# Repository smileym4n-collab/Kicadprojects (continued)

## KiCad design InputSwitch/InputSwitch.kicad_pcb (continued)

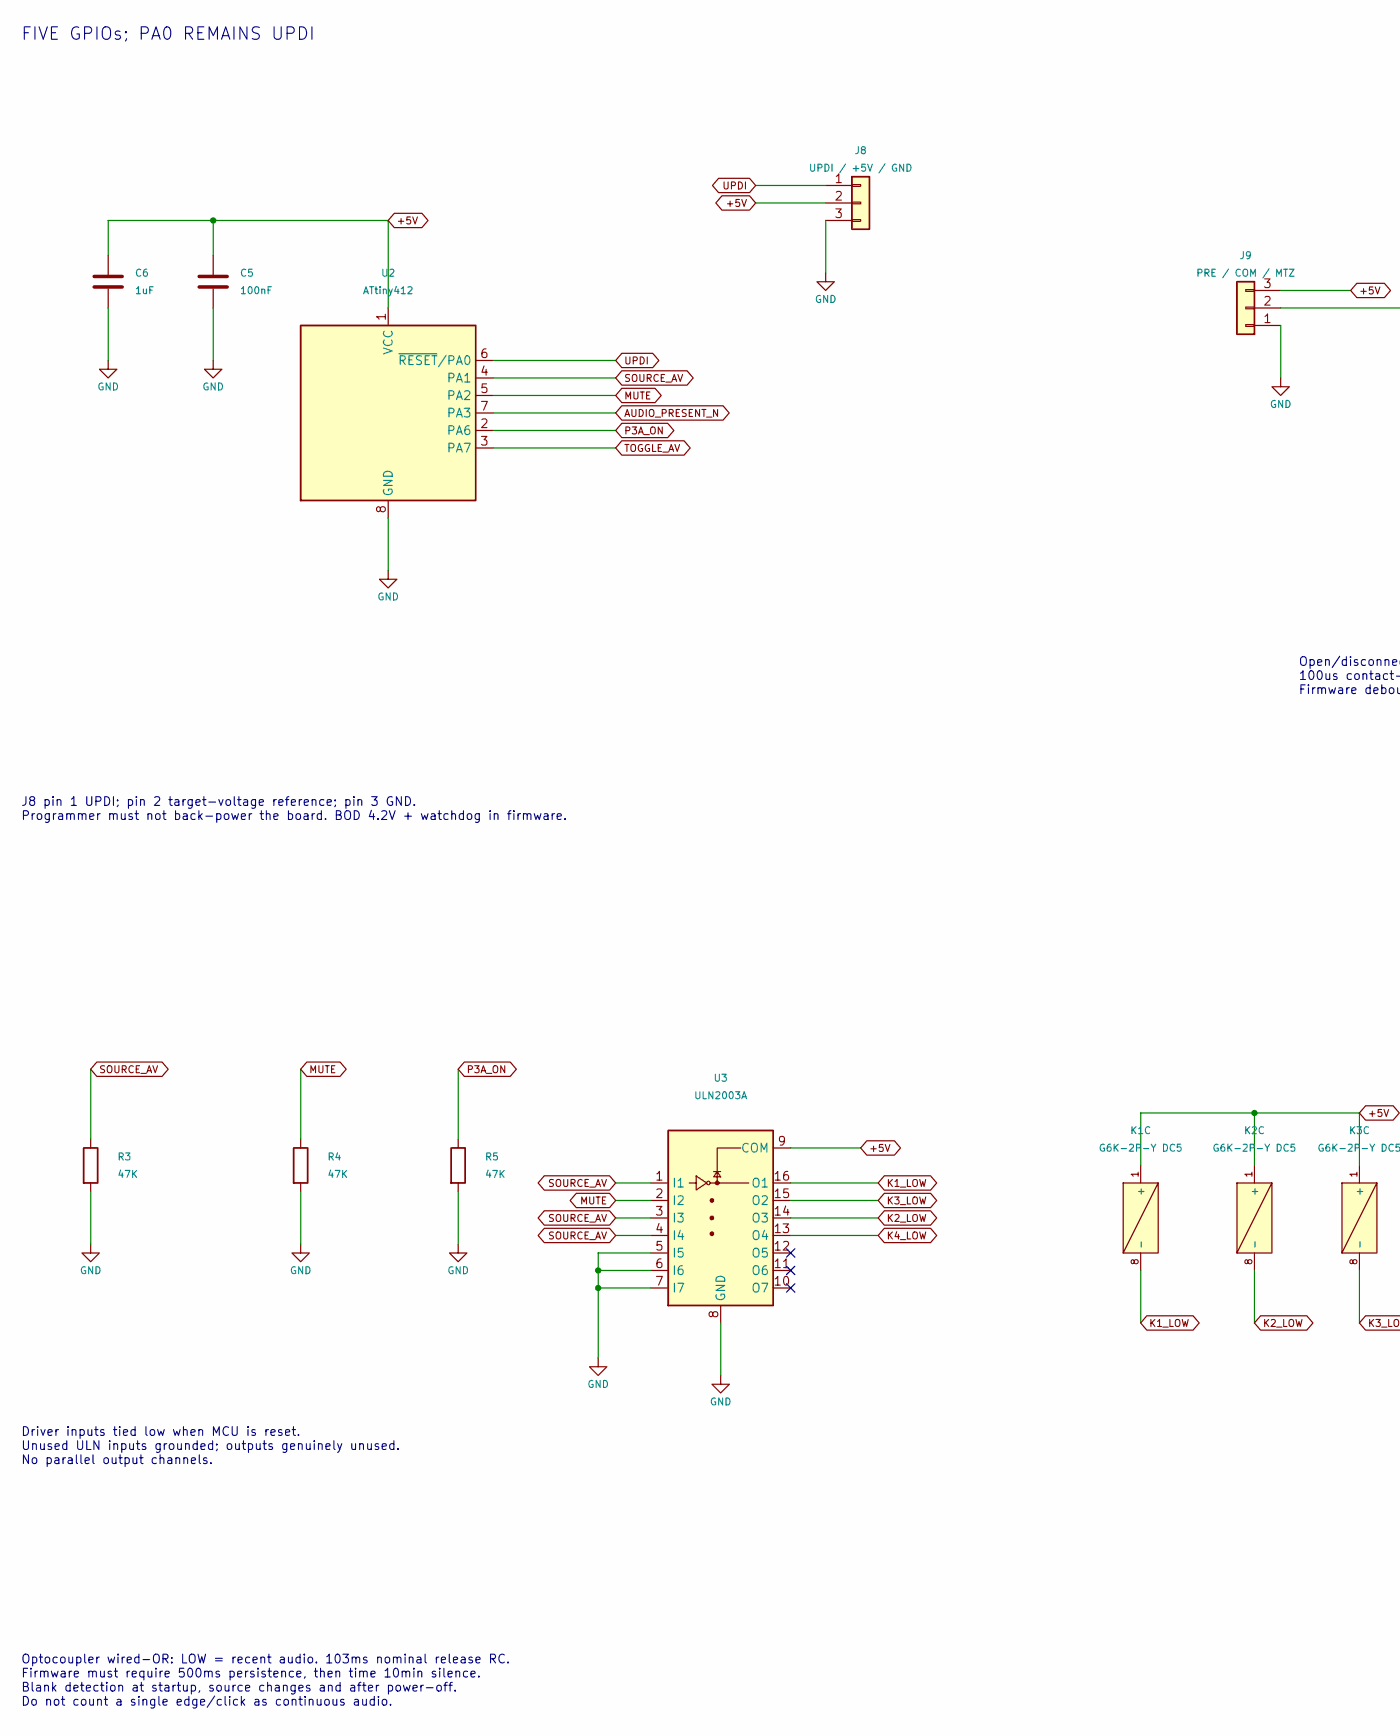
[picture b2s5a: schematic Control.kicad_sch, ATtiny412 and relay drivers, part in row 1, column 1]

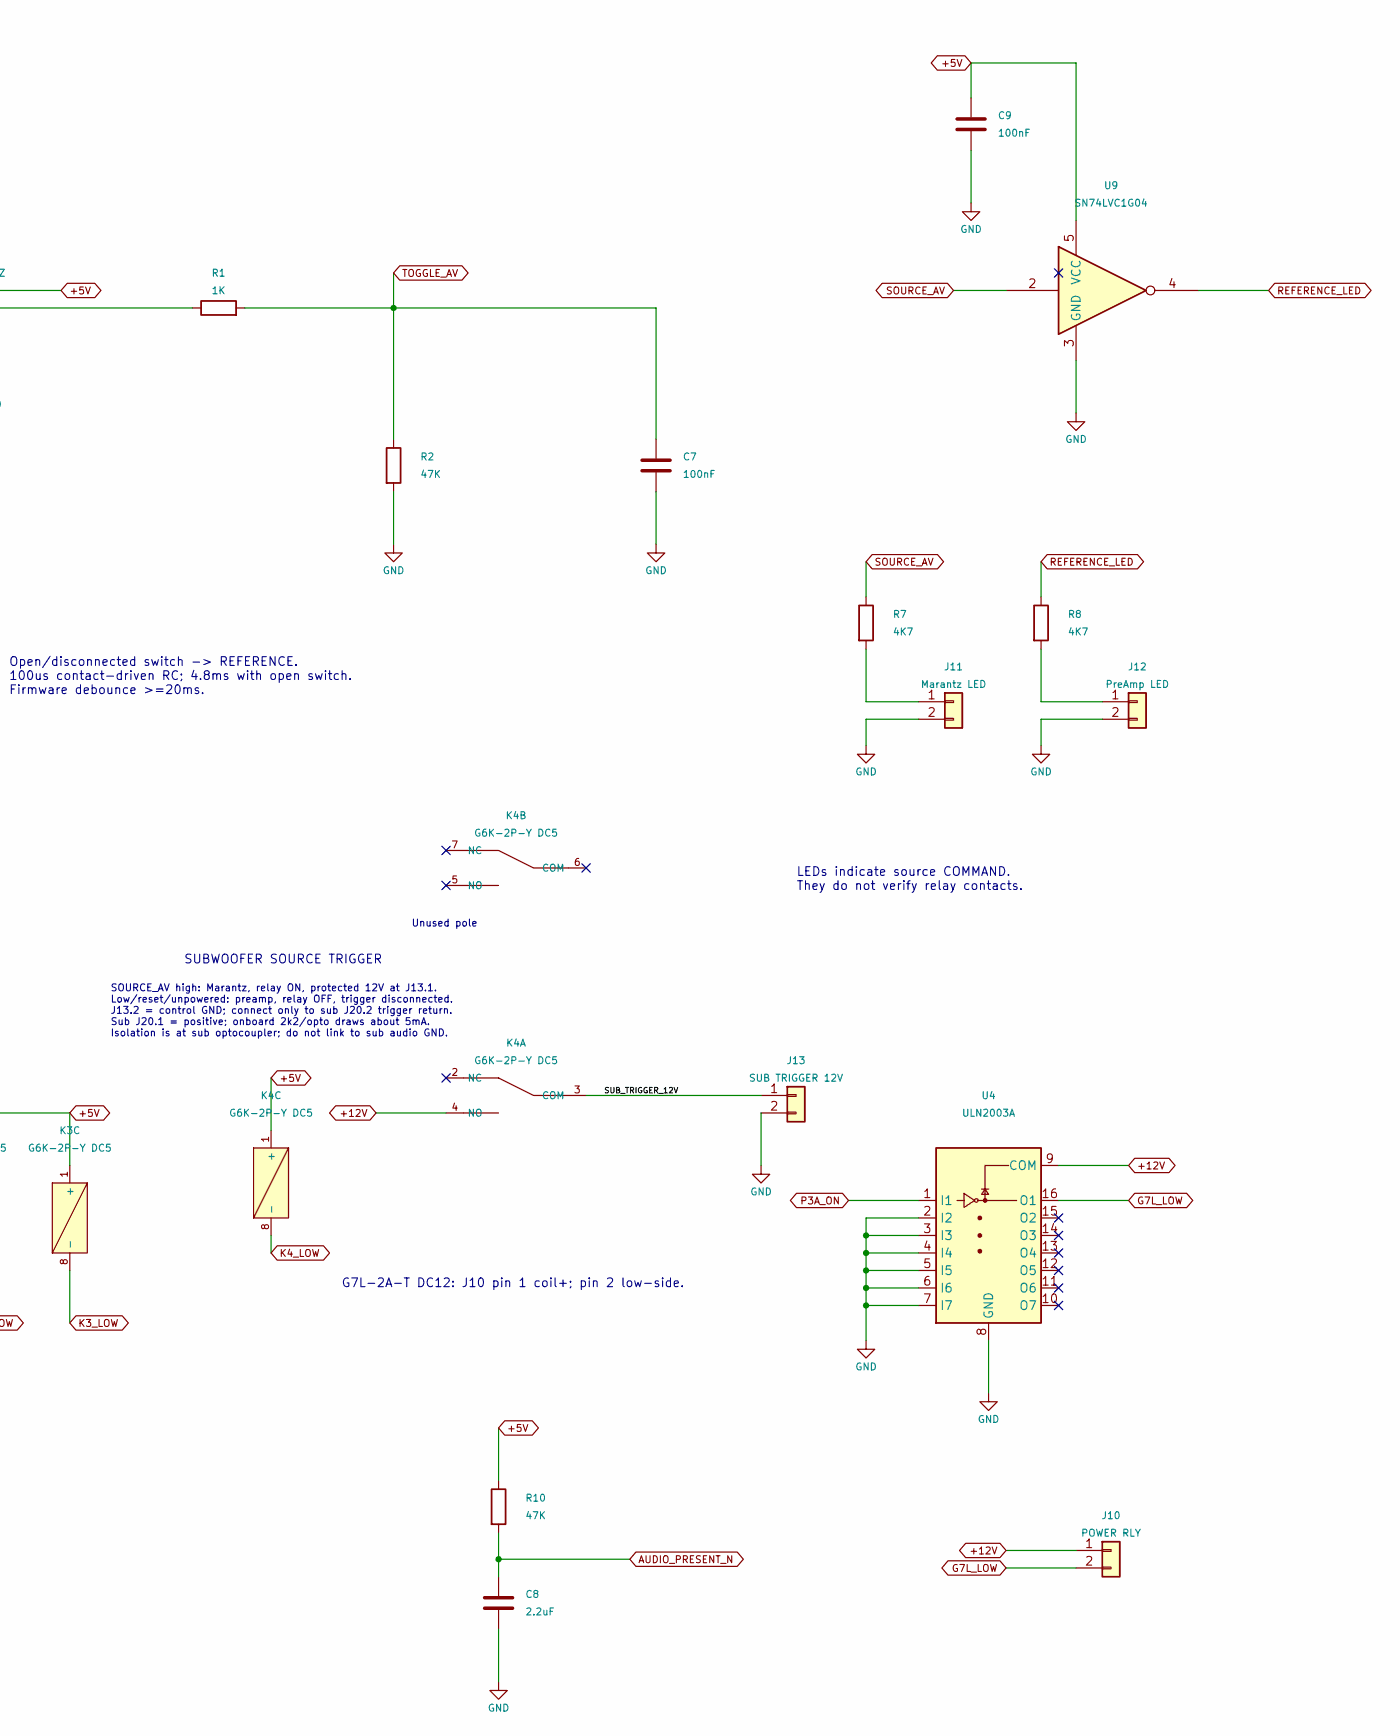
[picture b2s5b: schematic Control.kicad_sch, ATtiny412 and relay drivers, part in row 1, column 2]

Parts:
C5, C7, C9: 100nF; C_1206_3216Metric_Pad1.33x1.80mm_HandSolder
C6: 1uF; C_1206_3216Metric_Pad1.33x1.80mm_HandSolder
C8: 2.2uF; C_0805_2012Metric_Pad1.18x1.45mm_HandSolder
J8: UPDI / +5V / GND; JST_XH_B3B-XH-A_1x03_P2.50mm_Vertical
J9: PRE / COM / MTZ; JST_XH_B3B-XH-A_1x03_P2.50mm_Vertical
J10: POWER RLY; JST_XH_B2B-XH-A_1x02_P2.50mm_Vertical
J11: Marantz LED; JST_XH_B2B-XH-A_1x02_P2.50mm_Vertical
J12: PreAmp LED; JST_XH_B2B-XH-A_1x02_P2.50mm_Vertical
J13: SUB TRIGGER 12V; JST_XH_B2B-XH-A_1x02_P2.50mm_Vertical
K1, K2, K3, K4: G6K-2P-Y DC5; Relay_DPDT_Omron_G6K-2P-Y_Datasheet
R1: 1K; R_0805_2012Metric_Pad1.20x1.40mm_HandSolder
R2, R3, R4, R5, R10: 47K; R_0805_2012Metric_Pad1.20x1.40mm_HandSolder
R7, R8: 4K7; R_0805_2012Metric_Pad1.20x1.40mm_HandSolder
U2: ATtiny412; SOIC-8_3.9x4.9mm_P1.27mm
U3, U4: ULN2003A; SOIC-16_3.9x9.9mm_P1.27mm
U9: SN74LVC1G04; SOT-23-5

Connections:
+5V: C5.1, C6.1, C9.1, J8.2, J9.3, K1.1 (+), K2.1 (+), K3.1 (+), K4.1 (+), R10.1, U2.1 (VCC), U3.9 (COM), U9.5 (VCC); also elsewhere on the board
+12V: J10.1, K4.4 (NO), U4.9 (COM); also elsewhere on the board
/ATtiny412 and relay drivers/SUB_TRIGGER_12V: J13.1, K4.3 (COM)
AUDIO_PRESENT_N: C8.1, R10.2, U2.7 (PA3); also elsewhere on the board
G7L_LOW: J10.2, U4.16 (O1)
GND: C5.2, C6.2, C7.2, C8.2, C9.2, J8.3, J9.1, J11.2, J12.2, J13.2, R2.2, R3.2, R4.2, R5.2, U2.8 (GND), U3.5 (I5), U3.6 (I6), U3.7 (I7), U3.8 (GND), U4.2 (I2), U4.3 (I3), U4.4 (I4), U4.5 (I5), U4.6 (I6), U4.7 (I7), U4.8 (GND), U9.3 (GND); also elsewhere on the board
K1_LOW: K1.8 (-), U3.16 (O1)
K2_LOW: K2.8 (-), U3.14 (O3)
K3_LOW: K3.8 (-), U3.15 (O2)
K4_LOW: K4.8 (-), U3.13 (O4)
MUTE: R4.1, U2.5 (PA2), U3.2 (I2)
unnamed: J9.2, R1.1
unnamed: J11.1, R7.2
unnamed: J12.1, R8.2
P3A_ON: R5.1, U2.2 (PA6), U4.1 (I1)
REFERENCE_LED: R8.1, U9.4
SOURCE_AV: R3.1, R7.1, U2.4 (PA1), U3.1 (I1), U3.3 (I3), U3.4 (I4), U9.2
TOGGLE_AV: C7.1, R1.2, R2.1, U2.3 (PA7)
UPDI: J8.1, U2.6 (~RESET/PA0)

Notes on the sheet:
SUBWOOFER SOURCE TRIGGER
J8 pin 1 UPDI; pin 2 target-voltage reference; pin 3 GND. Programmer must not back-power the board. BOD 4.2V + watchdog in firmware.
FIVE GPIOs; PA0 REMAINS UPDI
LEDs indicate source COMMAND. They do not verify relay contacts.
G7L-2A-T DC12: J10 pin 1 coil+; pin 2 low-side.
Unused pole
Driver inputs tied low when MCU is reset. Unused ULN inputs grounded; outputs genuinely unused. No parallel output channels.
Open/disconnected switch -> REFERENCE. 100us contact-driven RC; 4.8ms with open switch. Firmware debounce >=20ms.
SOURCE_AV high: Marantz, relay ON, protected 12V at J13.1. Low/reset/unpowered: preamp, relay OFF, trigger disconnected. J13.2 = control GND; connect only to sub J20.2 trigger return. Sub J20.1 = positive; onboard 2k2/opto draws about 5mA. Isolation is at sub optocoupler; do not link to sub audio G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
Optocoupler wired-OR: LOW = recent audio. 103ms nominal release RC. Firmware must require 500ms persistence, then time 10min silence. Blank detection at startup, source changes and after power-off. Do not count a single edge/click as continuous audio.

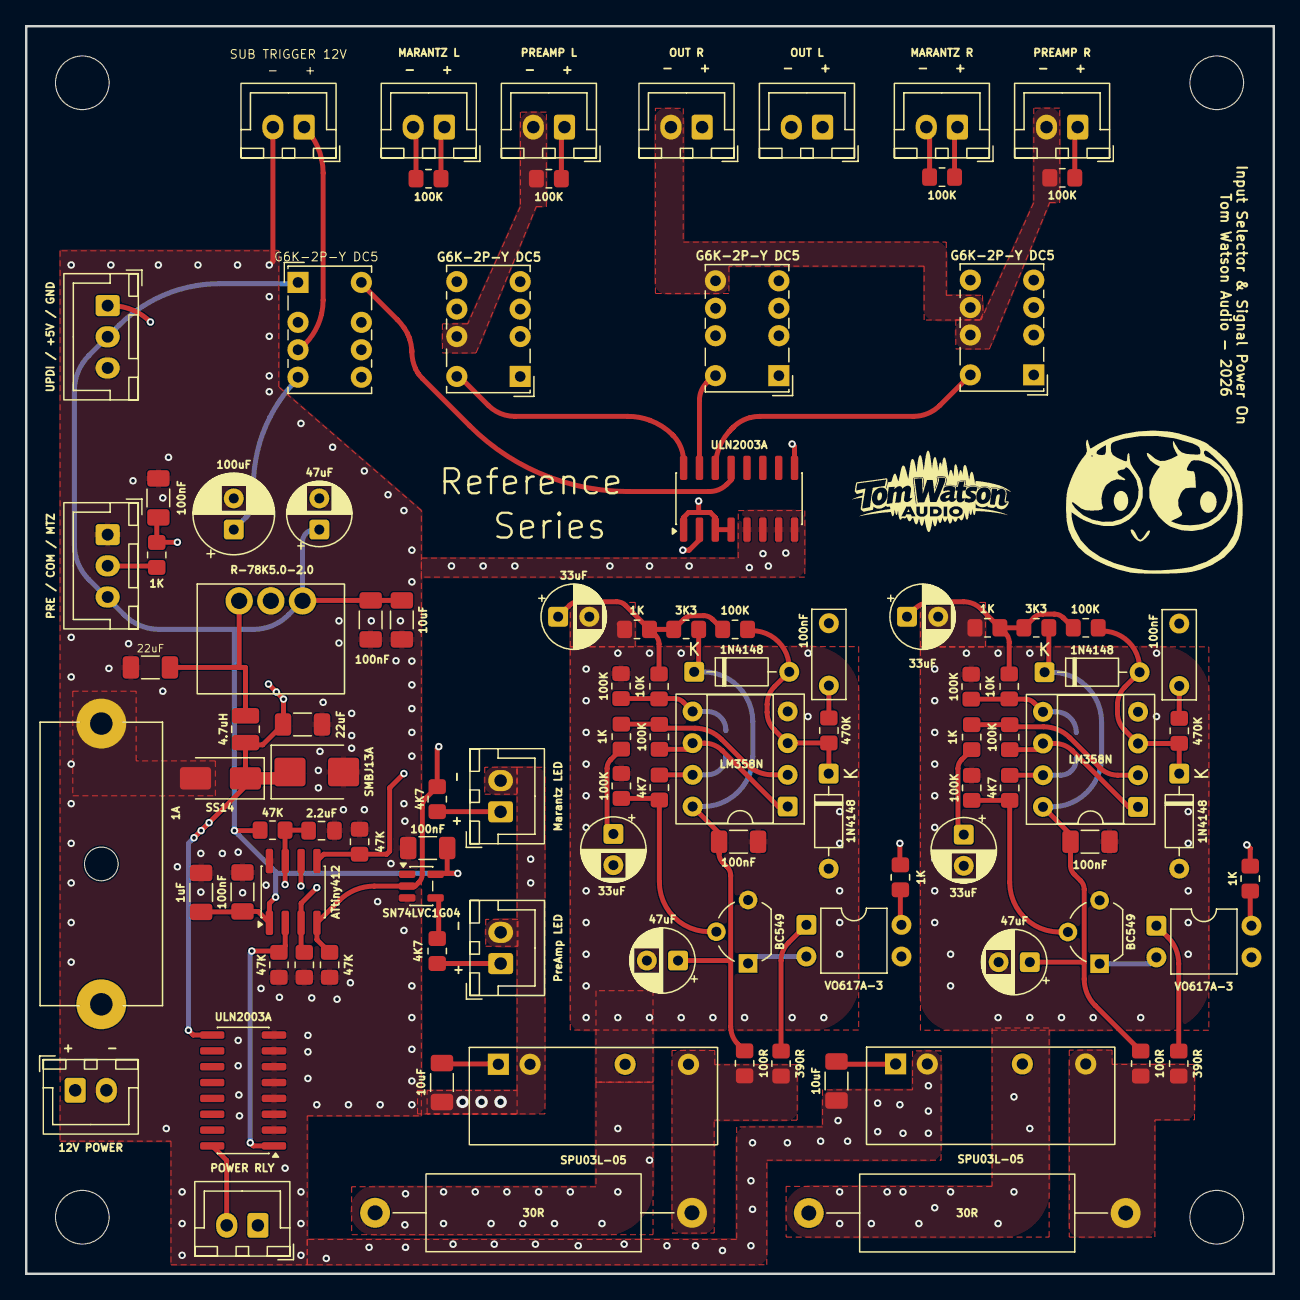
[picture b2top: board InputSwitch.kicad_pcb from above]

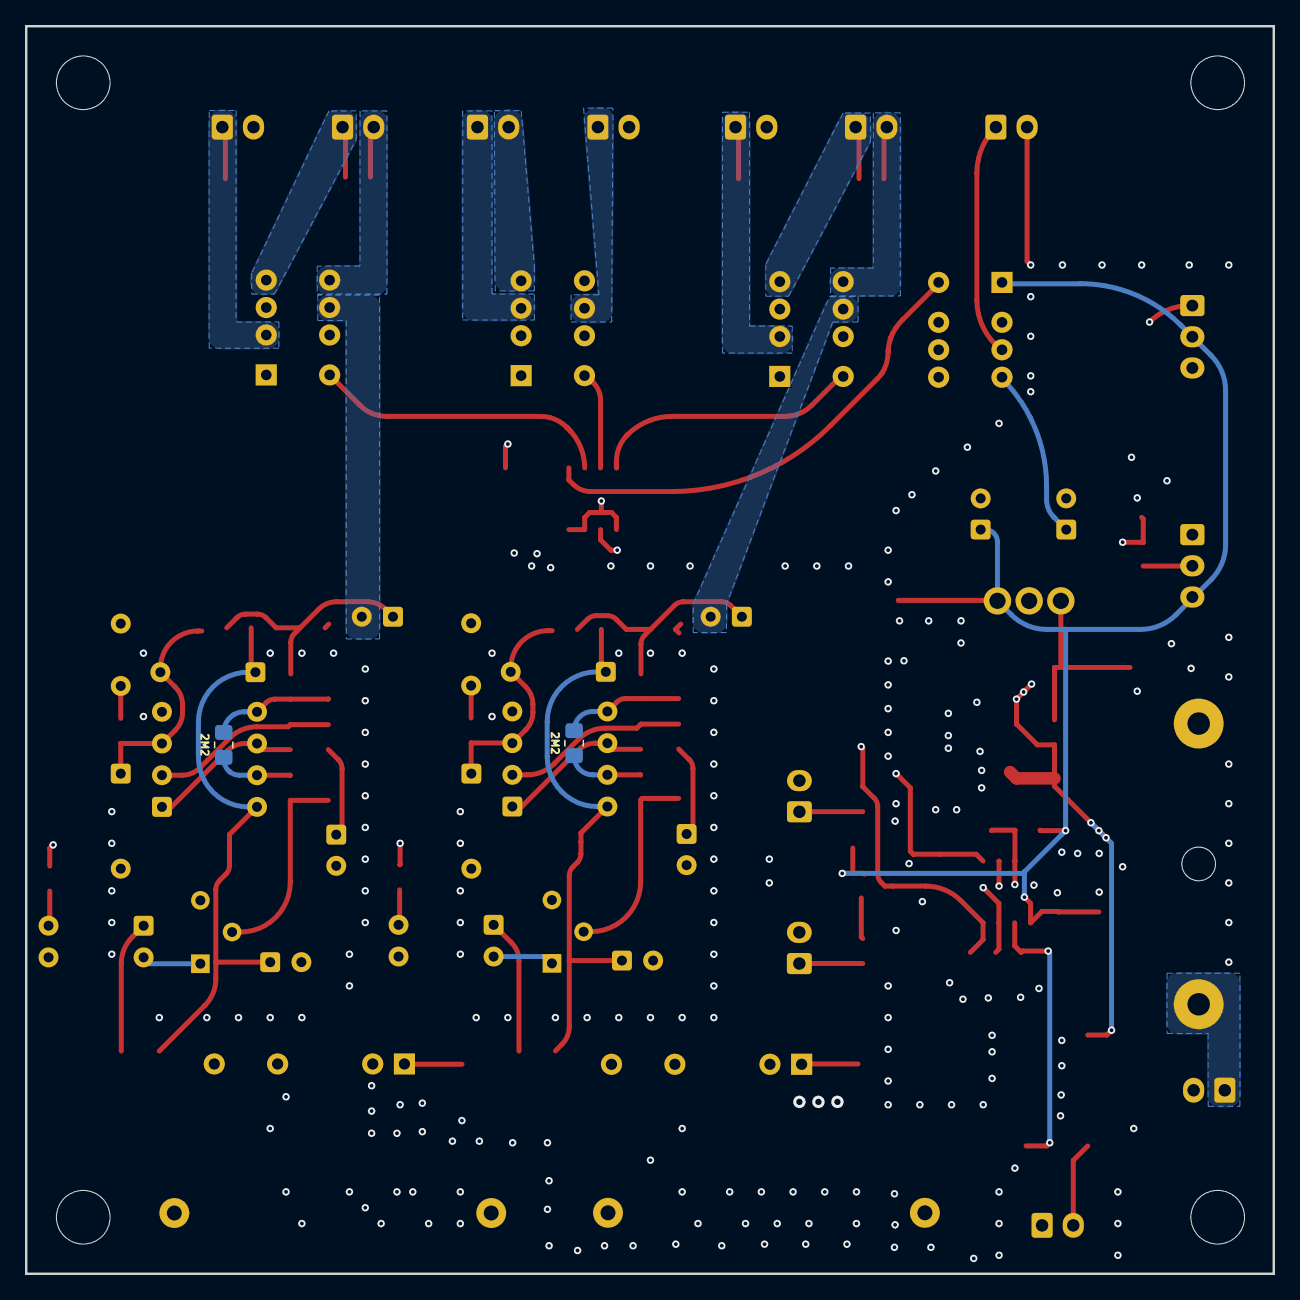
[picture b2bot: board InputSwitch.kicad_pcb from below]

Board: 4 copper layers, 100.0 x 100.0 mm, 107 parts (2 on the bottom side), 64 nets.

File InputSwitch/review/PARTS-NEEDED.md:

# InputSwitch parts needed

Inventory was checked live during this review. No stock was reserved or consumed and no orders were placed. Quantities listed as available are inventory records, not physical inspection. Match package and suffix exactly before assembly.

## Main purchases not found in inventory

| Qty | Part | Purpose / package |
|---:|---|---|
| 2 | Vishay **VO617A-3** | Detector optocouplers; standard DIP-4, 7.62 mm row spacing. |
| 1 | RECOM **R-78B5.0-2.0** | 12 V to 5 V buck module, SIP3, 2 A. Larger body than original 500 mA module; correct footprint assigned. |
| 1 | TI **SN74LVC1G04DBVR** | Source-LED inverter, DBV / SOT-23-5. |
| 2 | Vishay **PR03, 30R, 3W, 1%, copper leads** | Flameproof preload resistors; DIN0617, 25.4 mm formed pitch. Confirm exact suffix; 3 W rating requires copper-lead version. |
| 1 | Vishay **SS14** | Reverse-polarity blocking diode, SMA. No inventory hit in the initial search. |
| 1 | Littelfuse **SMBJ13A** | Unidirectional input TVS, SMB. |
| 1 | Omron **G7L-2A-T DC12** | External mains relay; no inventory record found. Omit purchase if already physically owned. |

**No isolated converters or 5.1 V reference zeners need to be bought.** Use two owned SPU03L-05 modules; one remains spare. Inventory ID416 is labelled “SPI03L-05”; the user identified the physical units as SPU03L-05. The inventory record was not edited.

Supplier references: [VO617A-3 at DigiKey UK](https://www.digikey.co.uk/en/products/detail/vishay-semicond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, [R-78B5.0-2.0 at DigiKey](https://www.digikey.com/en/products/detail/recom-power/R-78B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, [R-78B manufacturer](https://recom-power.com/en/rec-p-R-78B5.0-2.0.html), [PR03 manufacturer specification](https://www.vishay.com/docs/28729/pr010203.pdf). Confirm current UK stock, exact suffix and price before ordering. No suitable 30R power resistor was found in the inventory search; 330R and 0R33 records are not substitutes.

## Reuse from recorded stock

| Need | Inventory record | Recorded stock | Package / location |
|---:|---|---:|---|
| 3 | G6K-2P-Y, 5 V, ID 420 | 4, none reserved | Through-hole; location not recorded |
| 1 | ATtiny412, ID 80 | 6, none reserved | SOIC-8; SMD Parts |
| 2 | ULN2003A, ID 121 | 7, none reserved | ST SOIC-16; SMD Parts |
| 2 | SPU03L-05 (recorded SPI03L-05), ID 416 | 3, none reserved | SIP7; Voltage regulator drawer |
| 2 | LM358, ID 389 | 2, none reserved | TI DIP-8; Opamp drawer |
| 2 | BC549, ID 452 | 117, none reserved | TO-92; manufacturer/location not recorded |
| 4 | 1N4148, ID 138 | 63, none reserved | Through-hole; Parts drawer 2 |

The five DIP-16 ULN2003As (ID 120, Mixed ICs drawer) are not the package assigned in this schematic. Use the SOIC-16 stock above unless a package change is approved. Check the physical G6K markings really say DC5 and the BC549 lead order is C-B-E before assembly. The two LM358s use the entire recorded unreserved quantity. Five unreserved MCP6002 DIP-8 devices were also found (ID13, Opamps drawer); no op-amp substitution is necessary. See [suitability review](SPU03-LM358-REVIEW.md).

## Other build items

- Six two-pin JST XH headers for audio and two more for DC input/G7L coil; two three-pin JST XH headers for UPDI and toggle, with matching housings/crimps.
- SPDT ON-ON front toggle, two suitable indicator LEDs, six isolated RCA sockets or existing system harnesses, shielded audio wiring.
- Regulated isolated 12 V wall adapter, preferably ±2%, at least 1 A; suitable DC inlet/cable.
- T1A 5 x 20 mm fuse and holder. **Holder provision needs mechanical confirmation:** the assigned FX0457 library footprint and Bulgin's conflicting online orientation descriptions need comparison with the actual part/drawing before purchase/layout.
- Three test-point pins/pads and existing mounting hardware.
- Passives listed below; check drawer stock by exact value/rating before buying. SMD resistors and ceramics are **2012 metric**. The two 30R preload resistors are through-hole, 3 W, 1%; mount with ventilation and clearance from capacitors. They dissipate approximately 0.83 W each at nominal voltage. Use 1% resistors; thin-film in detector gain/threshold networks is sensible. No precision parts are needed in utility pull-downs or LED feeds.
- Main input capacitor C1: 100 µF / 35 V, 6.3 mm body, 2.5 mm lead spacing provision. Other radial electrolytics currently use 5 mm body / 2.5 mm pitch provisions. Confirm exact bought capacitor dimensions. C24/C44 are detector-branch film capacitors; their 5 mm pitch / body provision also needs an exact-part fit check.

The following grouped BOM is generated from the final exported netlist, so quantities and references correspond to the schematic. It is an assembly planning BOM, not an order-ready manufacturer-part-number BOM.

| Qty | Value / part | References | Package / provision |
|---:|---|---|---|
| 1 | +12V | TP1 | TestPoint_THTPad_D2.0mm_Drill1.0mm |
| 1 | +5V | TP2 | TestPoint_THTPad_D2.0mm_Drill1.0mm |
| 2 | 100R | R21, R41 | 2012 metric |
| 8 | 100k | R24, R25, R28, R31, R44, R45, R48, R51 | 2012 metric |
| 6 | 100n / 50V | C22, C4, C42, C5, C7, C9 | 2012 metric |
| 2 | 100n FILM / 50V | C24, C44 | C_Rect_L7.0mm_W2.0mm_P5.00mm |
| 1 | 100u / 35V | C1 | CP_Radial_D6.3mm_P2.50mm |
| 2 | 10k | R27, R47 | 2012 metric |
| 3 | 10u / 50V X7R | C2, C20, C40 | 2012 metric |
| 1 | 12V DC INPUT | J7 | JST_XH_B2B-XH-A_1x02_P2.50mm_Vertical |
| 4 | 1N4148 | D21, D22, D41, D42 | D_DO-35_SOD27_P7.62mm_Horizontal |
| 7 | 1k | R1, R26, R33, R34, R46, R53, R54 | 2012 metric |
| 1 | 1u / 25V | C6 | 2012 metric |
| 2 | 2M2 | R29, R49 | 2012 metric |
| 1 | 2u2 / 25V | C8 | 2012 metric |
| 2 | 30R / 3W / 1% | R20, R40 | R_Axial_DIN0617_L17.0mm_D6.0mm_P25.40mm_Horizontal |
| 4 | 33u / 16V | C23, C25, C43, C45 | CP_Radial_D5.0mm_P2.50mm |
| 2 | 390R | R32, R52 | 2012 metric |
| 2 | 3k3 | R22, R42 | 2012 metric |
| 2 | 470k | R23, R43 | 2012 metric |
| 5 | 47k | R10, R2, R3, R4, R5 | 2012 metric |
| 1 | 47u / 16V | C3 | CP_Radial_D5.0mm_P2.50mm |
| 2 | 47u / 25V | C21, C41 | CP_Radial_D5.0mm_P2.50mm |
| 4 | 4k7 | R30, R50, R7, R8 | 2012 metric |
| 1 | ATtiny412-SS | U2 | SOIC-8_3.9x4.9mm_P1.27mm |
| 1 | AV | D3 | LED_D3.0mm |
| 1 | AV L | J2 | JST_XH_B2B-XH-A_1x02_P2.50mm_Vertical |
| 1 | AV R | J4 | JST_XH_B2B-XH-A_1x02_P2.50mm_Vertical |
| 2 | BC549 | Q2, Q3 | TO-92_Inline |
| 3 | G6K-2P-Y DC5 | K1, K2, K3 | Relay_DPDT_Omron_G6K-2P-Y |
| 1 | G7L COIL ONLY | J10 | JST_XH_B2B-XH-A_1x02_P2.50mm_Vertical |
| 1 | GND | TP3 | TestPoint_THTPad_D2.0mm_Drill1.0mm |
| 2 | LM358N | U5, U7 | DIP-8_W7.62mm |
| 4 | M4 | H1, H2, H3, H4 | MountingHole_4.3mm_M4 |
| 1 | P3A L | J5 | JST_XH_B2B-XH-A_1x02_P2.50mm_Vertical |
| 1 | P3A R | J6 | JST_XH_B2B-XH-A_1x02_P2.50mm_Vertical |
| 1 | R-78B5.0-2.0 | U1 | R78B_2A_SIP3 |
| 1 | REFERENCE | D4 | LED_D3.0mm |
| 1 | REFERENCE L | J1 | JST_XH_B2B-XH-A_1x02_P2.50mm_Vertical |
| 1 | REFERENCE R | J3 | JST_XH_B2B-XH-A_1x02_P2.50mm_Vertical |
| 1 | SMBJ13A | D2 | D_SMB |
| 1 | SN74LVC1G04DBV | U9 | SOT-23-5 |
| 1 | SPDT: REF / COM / AV | J9 | JST_XH_B3B-XH-A_1x03_P2.50mm_Vertical |
| 2 | SPU03L-05 | U10, U11 | SPU03L_05_SIP7 |
| 1 | SS14 | D1 | D_SMA |
| 1 | T1A | F1 | Fuseholder_Cylinder-5x20mm_Bulgin_FX0457_Horizontal_Closed |
| 1 | ULN2003A (12V COIL) | U4 | SOIC-16_3.9x9.9mm_P1.27mm |
| 1 | ULN2003A (5V COILS) | U3 | SOIC-16_3.9x9.9mm_P1.27mm |
| 1 | UPDI / +5V / GND | J8 | JST_XH_B3B-XH-A_1x03_P2.50mm_Vertical |
| 2 | VO617A-3 | U6, U8 | DIP-4_W7.62mm |

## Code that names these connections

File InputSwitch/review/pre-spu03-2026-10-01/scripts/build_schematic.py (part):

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 nc,co,no=(2,3,4) if ch=='L' else (7,6,5)
 a.net(mute,nc,'SEL_'+ch+'_SIGNAL',-8,0)
 jrout=conn(a,'J5' if ch=='L' else 'J6','P3A '+ch,143,y,rot=0)
 a.w(a.p(mute,co),a.p(jrout,1));a.label('P3A_'+ch+'_SIGNAL',a.at(125,y))
 p=a.p(mute,no);b=a.at(102,y+6);d=a.at(137,y+6)
 a.w(p,a.at(102,y+1),b,d,a.at(137,y+1),a.p(jrout,2));a.w(b,(b[0],b[1]+2*U));a.label('SEL_'+ch+'_RETURN',(b[0],b[1]+2*U),True)
 a.text(ch+' channel: no common GND',8,y+22)
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 else:s.net(tp,1,net,0,3)
s.text('NO PCB MAINS. Do not update the old PCB from this schematic until layout work is authorised.',8,100,1.5)
# Control
s=ctl;s.text('FIVE GPIOs; PA0 REMAINS UPDI',8,7,1.8)
u=s.add('MCU_Microchip_ATtiny:ATtiny412-SS','U2','ATtiny412-SS',29,29)
s.net(u,1,'+5V',0,-3);s.ground(u,8)
for n,net in [(6,'UPDI'),(4,'SOURCE_AV'),(5,'MUTE'),(7,'AUDIO_PRESENT_N'),(2,'P3A_ON'),(3,'TOGGLE_AV')]:s.net(u,n,net,7,0)
caprail(s,'C5','100n / 50V',10,25,'+5V');caprail(s,'C6','1u / 25V',10,41,'+5V')
j=conn(s,'J8','UPDI / +5V / GND',56,17,3,rot=0)
s.net(j,1,'UPDI',-4,0);s.net(j,2,'+5V',-4,0);s.ground(j,3)
s.text('J8 pin 1 UPDI; pin 2 target-voltage reference; pin 3 GND.\nProgrammer must not back-power the board. BOD 4.2V + watchdog in firmware.',8,51)
# Toggle connector and RC
j=conn(s,'J9','SPDT: REF / COM / AV',78,23,3,rot=180)
s.ground(j,1,3)
rr=r(s,'R1','1k',93,23,90);s.w(s.p(j,2),s.at(88,23),s.p(rr,1));s.net(j,3,'+5V',4,0)
node=s.at(103,23);s.w(s.p(rr,2),node);s.w(node,(node[0],node[1]-2*U));s.label('TOGGLE_AV',(node[0],node[1]-2*U),True)
rp=r(s,'R2','47k',103,32);s.w(node,s.p(rp,1));s.ground(rp,2)
cc=c(s,'C7','100n / 50V',118,32);s.w(node,s.at(118,23),s.p(cc,1));s.ground(cc,2)
s.text('Open/disconnected switch -> REFERENCE.\n100us contact-driven RC; 4.8ms with open switch.\nFirmware debounce >=20ms.',81,43)
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 rt=R(7,'10k',77,64);s.net(rt,1,bias,0,-3,False);tn=s.at(77,71);s.w(s.p(rt,2),tn,s.p(ub,5))
 rb2=R(8,'100k',77,91);s.w(tn,s.at(72,71),s.at(72,89.5),s.p(rb2,1));retpin(rb2,2)
 rh=R(9,'1M',89,57,90);s.w(s.p(rh,1),s.at(81,57),s.at(81,71),tn)
 cp=s.at(96,72);s.w(s.p(ub,7),cp,s.at(96,57),s.p(rh,2));s.label('DETECT_PULSE',cp)
 # BJT takes optocoupler LED current off the LM358 output.
 rr=R(10,'10k',106,72,90);s.w(cp,s.p(rr,1))
 qb=s.add('Transistor_BJT:BC549',qref,'BC549',116,72,fp='Package_TO_SOT_THT:TO-92_Inline',ds='https://www.onsemi.com/pdf/datasheet/bc550-d.pdf');s.w(s.p(rr,2),s.p(qb,2));retpin(qb,3)
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  if upper:
   s.net(dd,1,quiet,0,-2);s.net(dd,2,'SENSE_INPUT',0,2,False)
  else:
   s.net(dd,1,'SENSE_INPUT',0,-2,False);retpin(dd,2)
 s.label('SENSE_INPUT',node)
 s.text('Branch clamps only;\nnever in the main audio path.',8,103)
for i,(x,y) in enumerate([(80,23),(90,23),(100,23),(110,23)],1):
 power.add('Mechanical:MountingHole',f'H{i}','M4',x,y,fp='MountingHole:MountingHole_4.3mm_M4')
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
